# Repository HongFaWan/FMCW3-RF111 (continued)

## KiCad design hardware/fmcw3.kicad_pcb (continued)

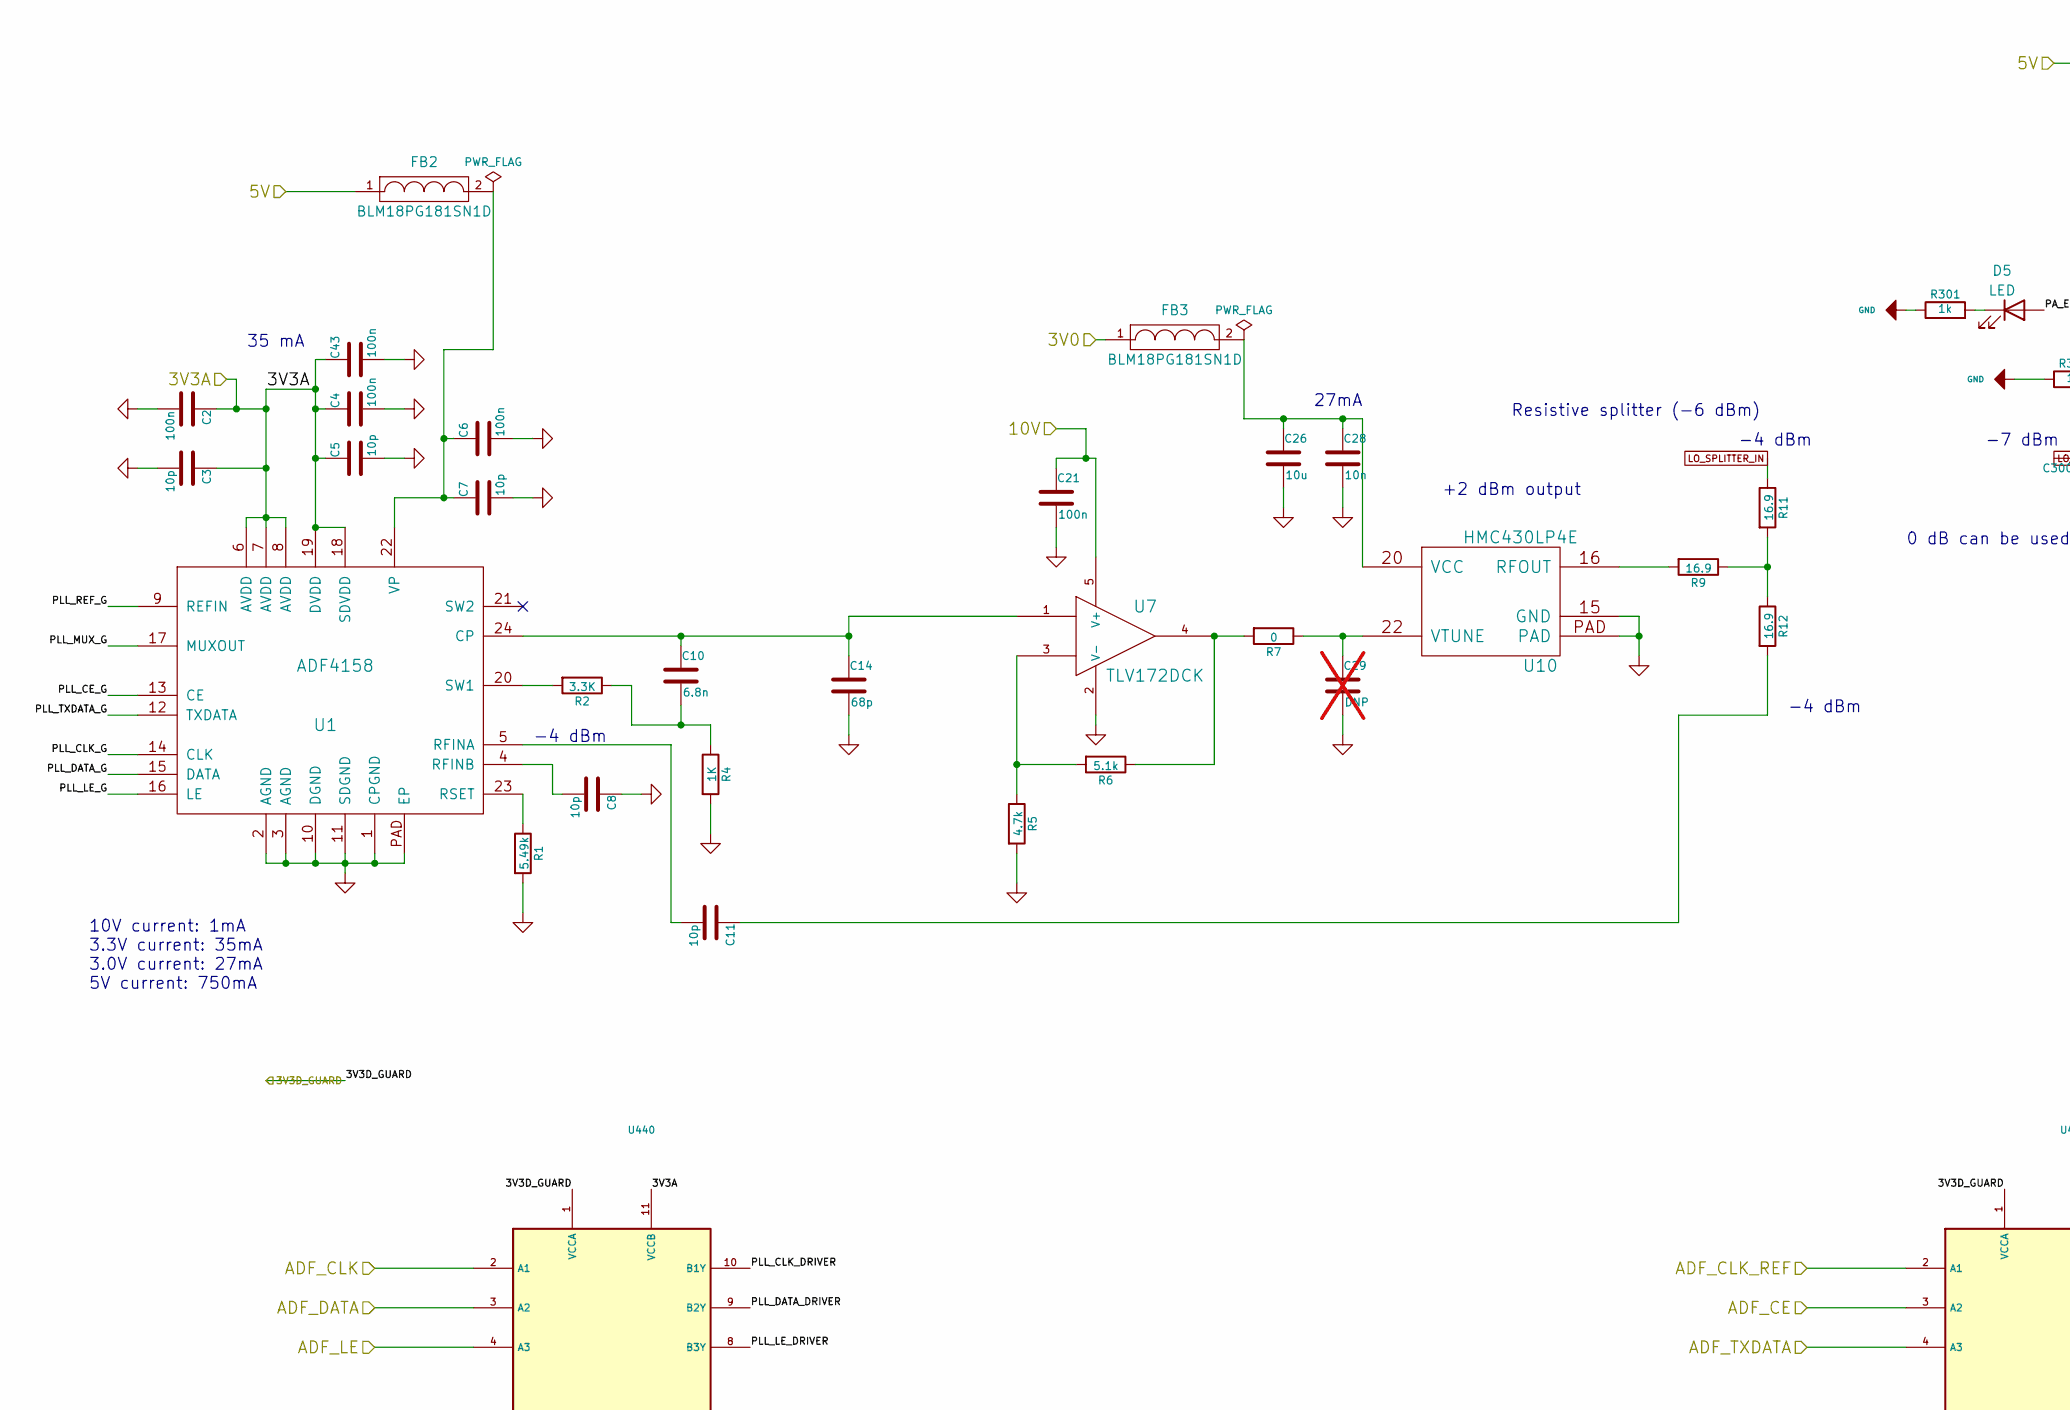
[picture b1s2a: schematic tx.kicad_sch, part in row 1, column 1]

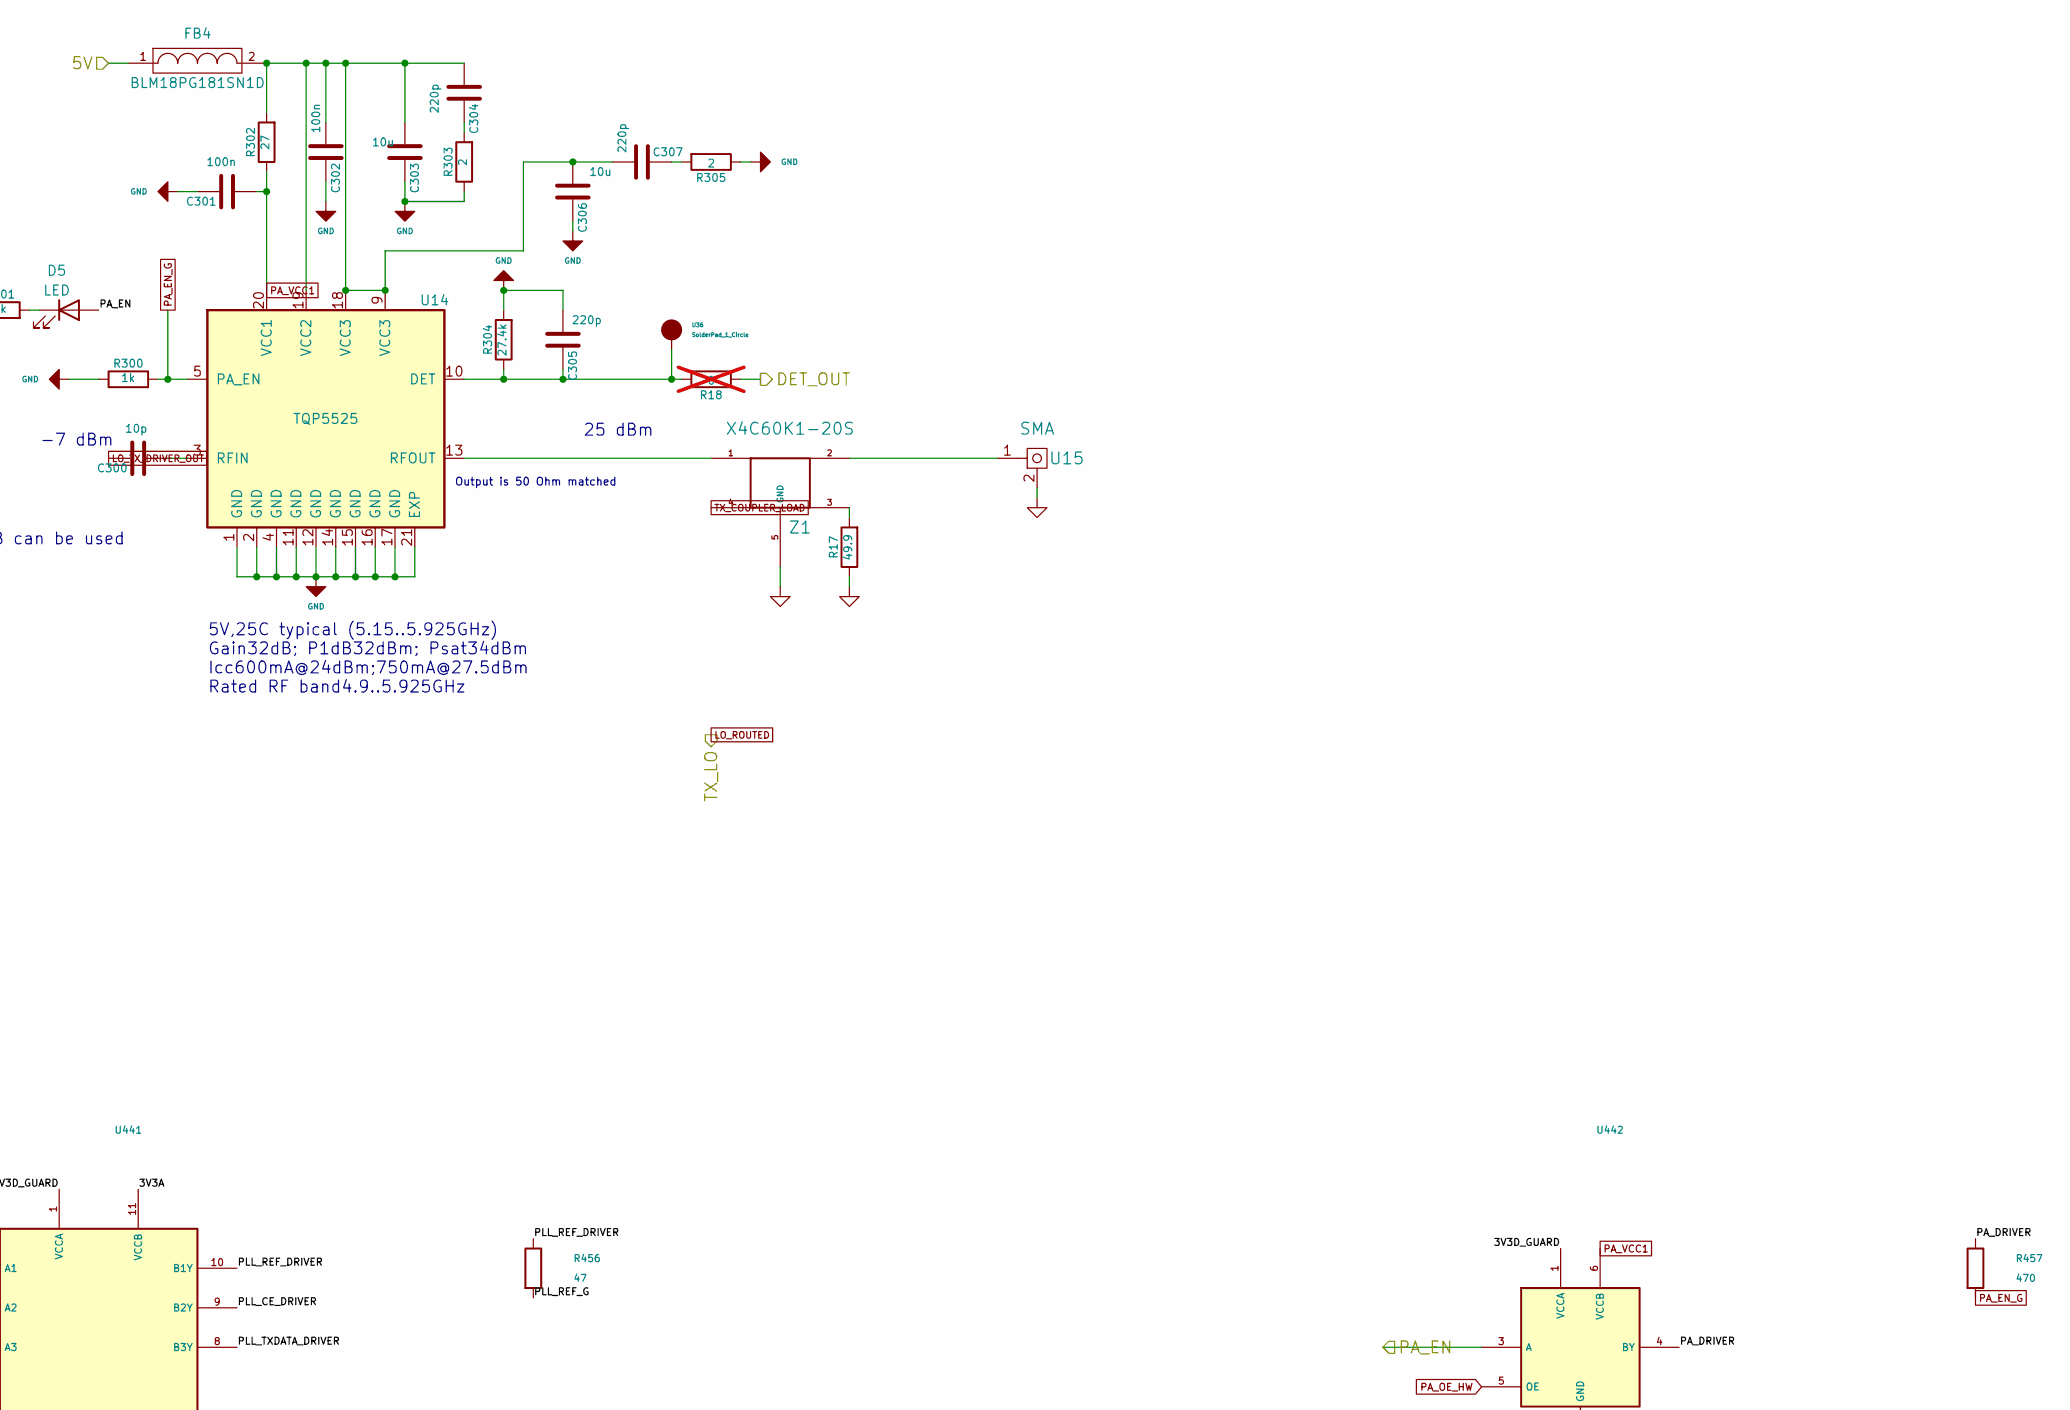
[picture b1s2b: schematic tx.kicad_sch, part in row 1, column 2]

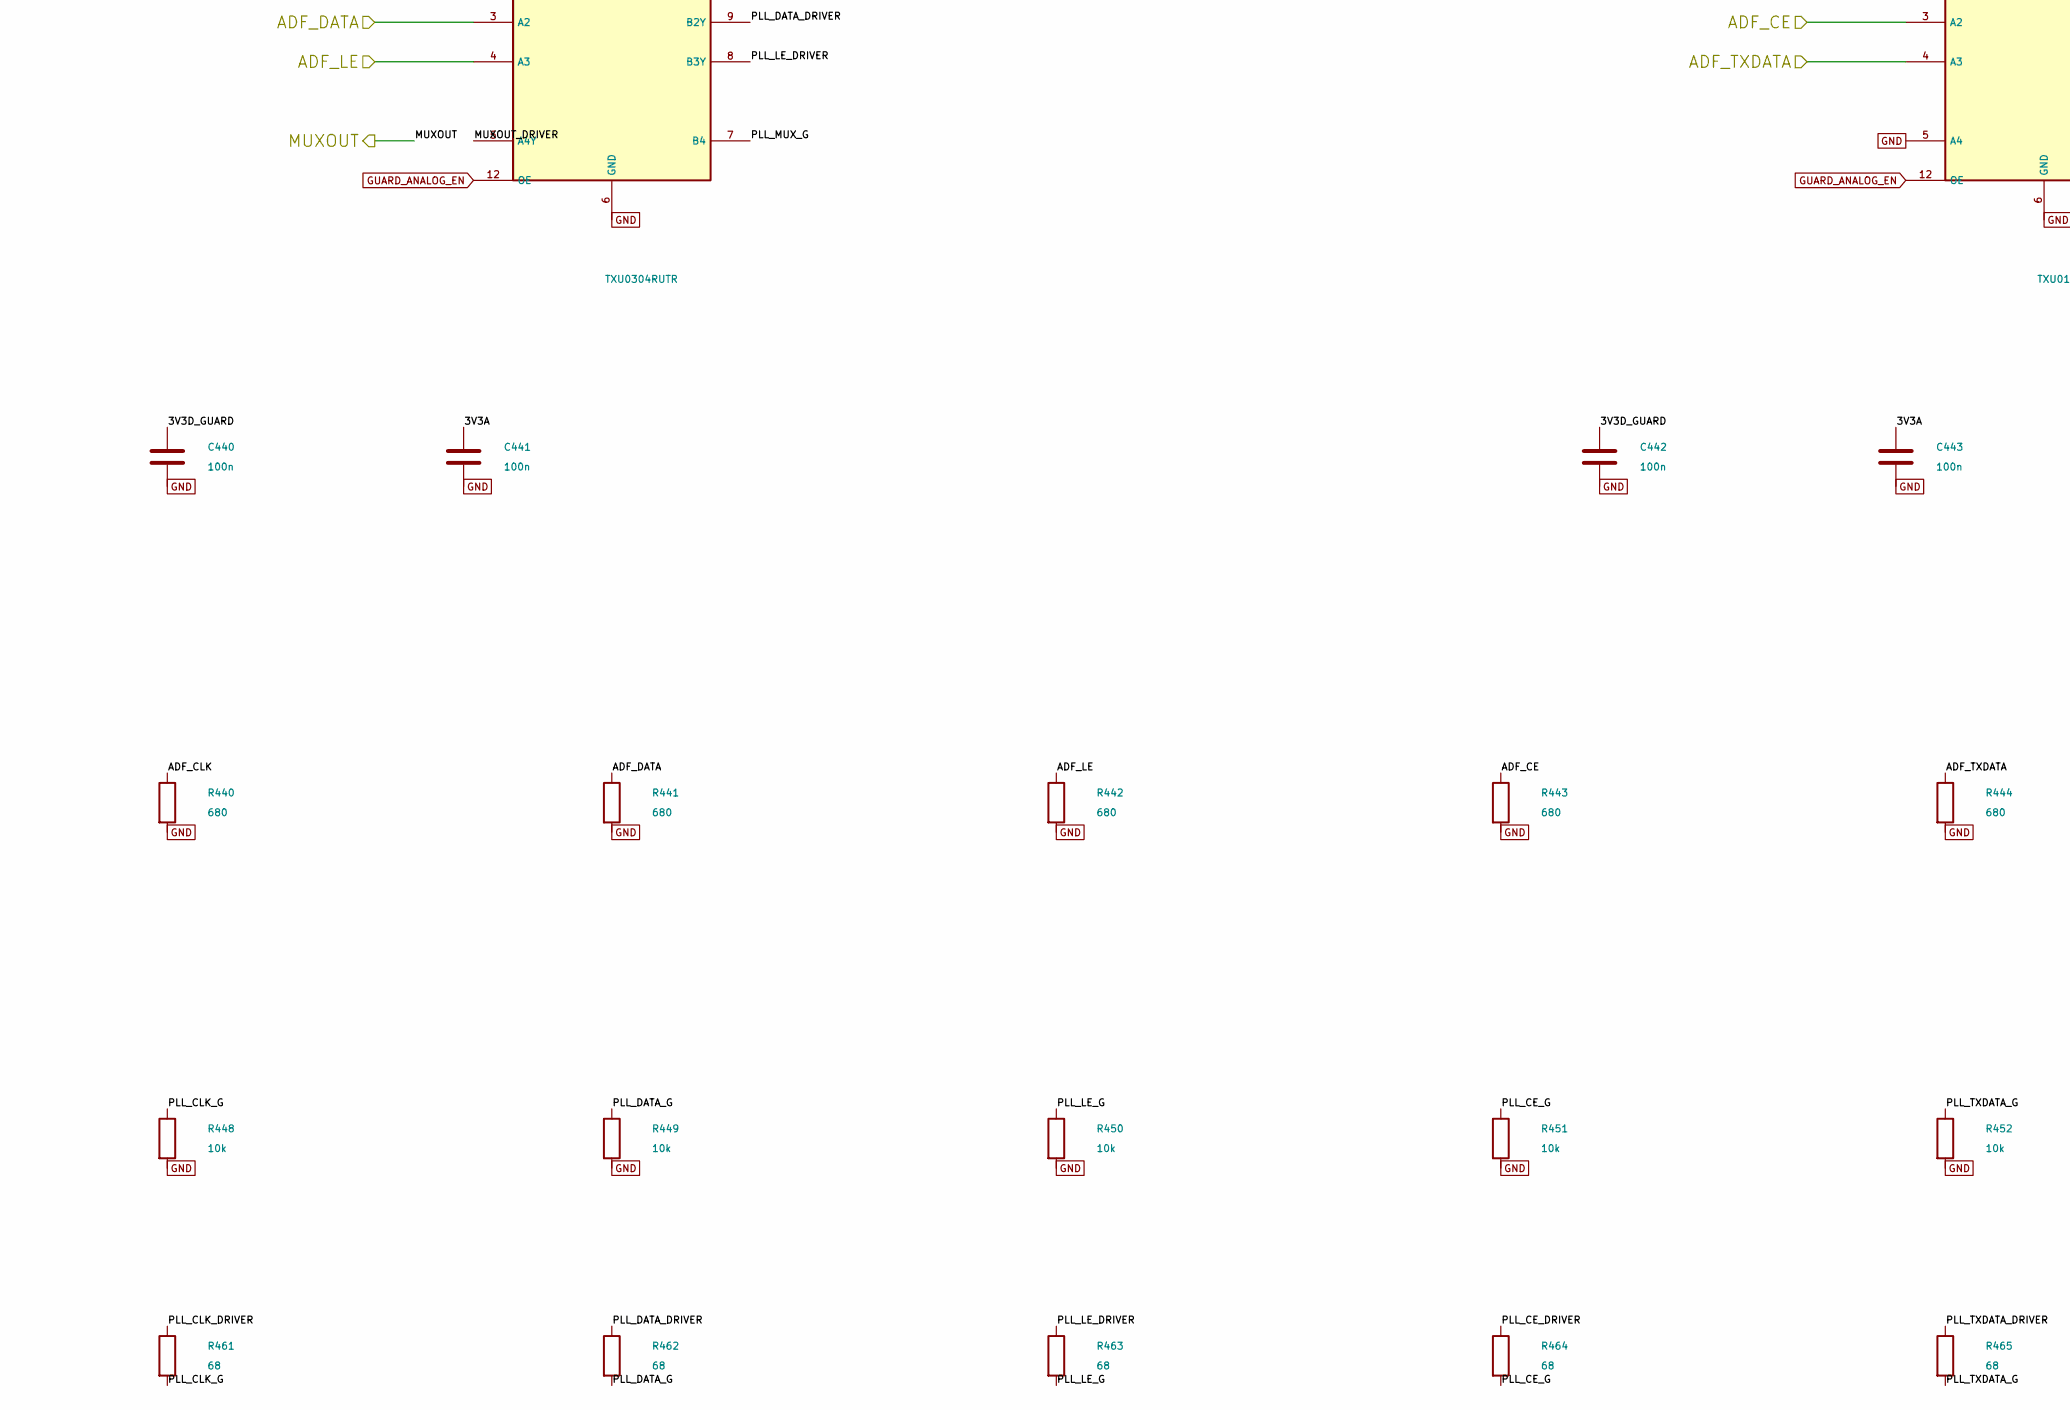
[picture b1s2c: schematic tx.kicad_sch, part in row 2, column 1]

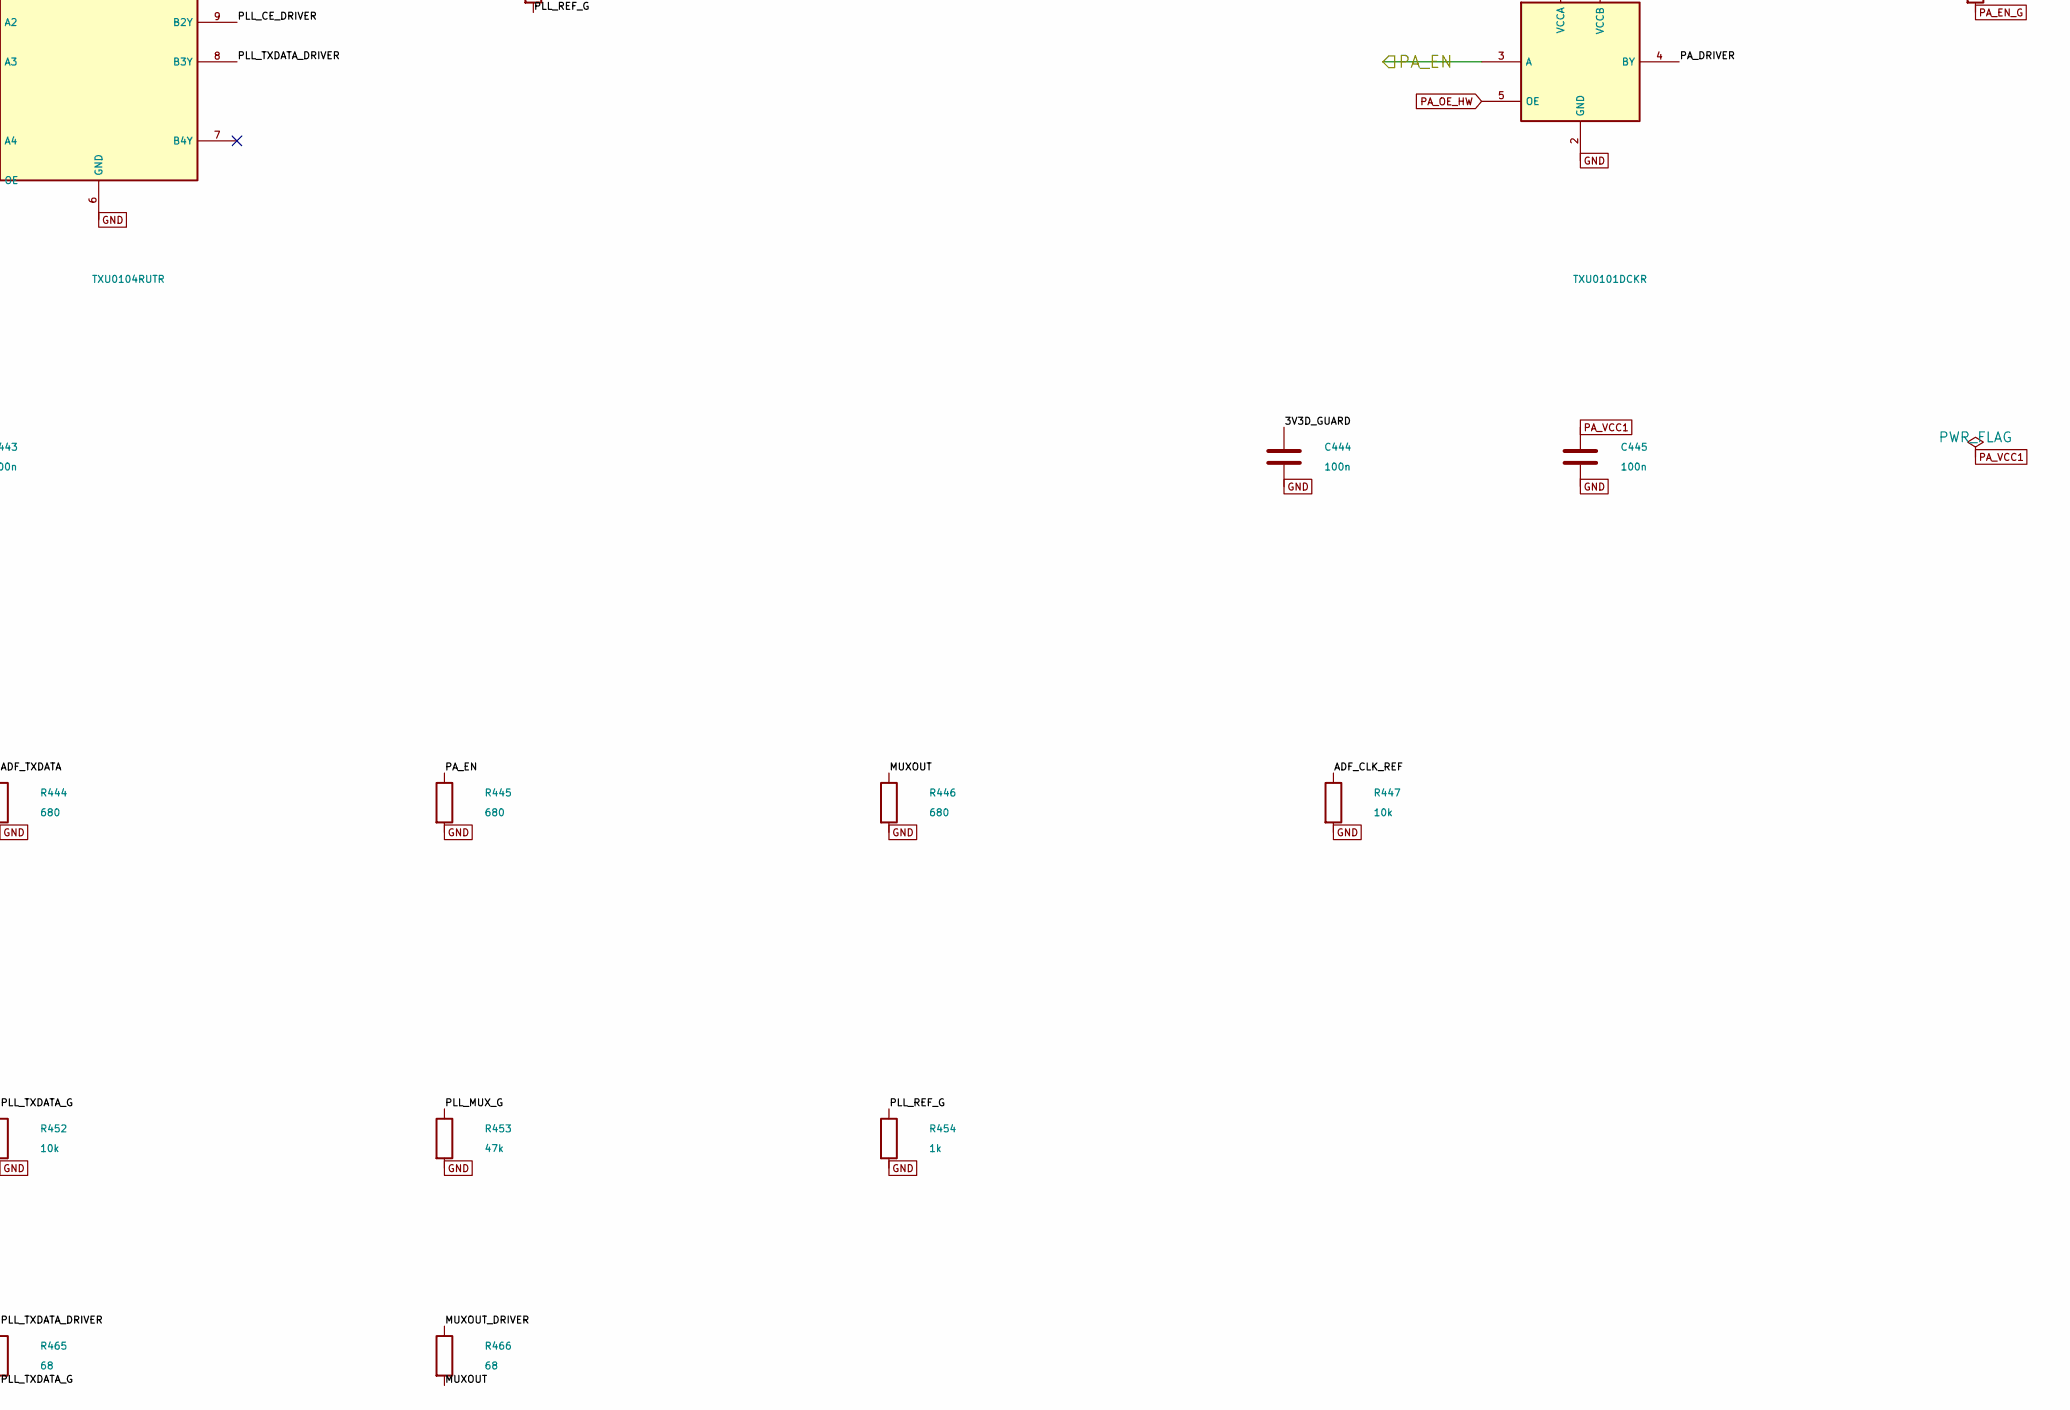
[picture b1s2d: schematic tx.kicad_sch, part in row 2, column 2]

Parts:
C2, C4, C6, C21, C43, C301, C302: 100n; SMD_0402
C3, C5, C7, C8, C11, C300: 10p; SMD_0402
C10: 6.8n; SMD_0402
C14: 68p; SMD_0402
C26, C303, C306: 10u; SMD_0805
C28: 10n; SMD_0402
C29: DNP; SMD_0402; not fitted
C304, C305, C307: 220p; SMD_0402
C440, C441, C442, C443, C444, C445: 100n; C_0402_Murata_GRM155_Mount22; Voltage 50V; Tolerance 10%; MPN GRM155R71H104KE14D; LCSC C77020
D5: LED; Diode_0603
FB2, FB3, FB4: BLM18PG181SN1D; SMD_0603
R1: 5.49k; SMD_0402
R2: 3.3K; SMD_0402
R4: 1K; SMD_0402
R5: 4.7k; SMD_0402
R6: 5.1k; SMD_0402; MPN RC0402FR-075K1L; LCSC C105872
R7: 0; SMD_0402
R9, R11, R12: 16.9; SMD_0402
R17: 49.9; SMD_0402
R18: 0; SMD_0402; not fitted
R300, R301: 1k; SMD_0402
R302: 27; SMD_0402
R303, R305: 2; SMD_0603
R304: 27.4k; SMD_0402
R440, R441, R442, R443, R444, R445, R446: 680; R_0402_Yageo_Mount22; MPN RC0402FR-07680RL; LCSC C137948
R447, R448, R449, R450, R451, R452: 10k; R_0402_Yageo_Mount22; MPN RT0402BRD0710KL; LCSC C190095
R453: 47k; R_0402_Yageo_Mount22; MPN RC0402FR-0747KL; LCSC C93943
R454: 1k; R_0402_Yageo_Mount22; MPN RC0402FR-071KL; LCSC C106235
R456: 47; R_0402_Yageo_Mount22; MPN RC0402FR-0747RL; LCSC C137973
R457: 470; R_0402_Yageo_Mount22; MPN RC0402FR-07470RL
R461, R462, R463, R464, R465, R466: 68; R_0402_Yageo_Mount22; MPN RC0402FR-0768RL; LCSC C163455
U1: ADF4158; VFQFN-24
U7: TLV172DCK; SOT-353_SC-70-5
U10: HMC430LP4E; VQFN-24; MPN HMC430LP4ETR
U14: TQP5525; QFN-20-1EP_4x4mm_P0.5mm_EP2.5x2.5mm_ThermalVias
U15: SMA; CONSMA003.062
U36: SolderPad_1_Circle; SolderPad_1_1.5mm_SMD_Circle
U440: TXU0304RUTR; TI_RUT12_0p7x0p2_MFR; MPN TXU0304RUTR; LCSC C2959768
U441: TXU0104RUTR; TI_RUT12_0p7x0p2_MFR; MPN TXU0104RUTR; LCSC C5187176
U442: TXU0101DCKR; TI_DCK6_0p9x0p4_MFR; MPN TXU0101DCKR; LCSC C5217868
Z1: X4C60K1-20S; X4C60K1_20S; MPN X4C60K1-20S

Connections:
/3V0: FB3.1; also elsewhere on the board
/3V3A: C2.1, C3.1, C4.1, C5.1, C43.1, C441.1, C443.1, U1.6 (AVDD), U1.7 (AVDD), U1.8 (AVDD), U1.18 (SDVDD), U1.19 (DVDD), U440.11 (VCCB), U441.11 (VCCB); also elsewhere on the board
/5V: FB2.1, FB4.1; also elsewhere on the board
/ADF_CE: R443.1, U441.3 (A2); also elsewhere on the board
/ADF_CLK: R440.1, U440.2 (A1); also elsewhere on the board
/ADF_CLK_REF: R447.1, U441.2 (A1); also elsewhere on the board
/ADF_DATA: R441.1, U440.3 (A2); also elsewhere on the board
/ADF_LE: R442.1, U440.4 (A3); also elsewhere on the board
/ADF_MUXOUT: R446.1, R466.2; also elsewhere on the board
/ADF_TXDATA: R444.1, U441.4 (A3); also elsewhere on the board
/DET_OUT: R18.1; also elsewhere on the board
/PA_EN: D5.2 (A), R445.1, U442.3 (A); also elsewhere on the board
/tx/MUXOUT_DRIVER: R466.1, U440.5 (A4Y)
/tx/PA_DRIVER: R457.1, U442.4 (BY)
/tx/PLL_CE_DRIVER: R464.1, U441.9 (B2Y)
/tx/PLL_CE_G: R451.1, R464.2, U1.13 (CE)
/tx/PLL_CLK_DRIVER: R461.1, U440.10 (B1Y)
/tx/PLL_CLK_G: R448.1, R461.2, U1.14 (CLK)
/tx/PLL_DATA_DRIVER: R462.1, U440.9 (B2Y)
/tx/PLL_DATA_G: R449.1, R462.2, U1.15 (DATA)
/tx/PLL_LE_DRIVER: R463.1, U440.8 (B3Y)
/tx/PLL_LE_G: R450.1, R463.2, U1.16 (LE)
/tx/PLL_MUX_G: R453.1, U1.17 (MUXOUT), U440.7 (B4)
/tx/PLL_REF_DRIVER: R456.1, U441.10 (B1Y)
/tx/PLL_REF_G: R454.1, R456.2, U1.9 (REFIN)
/tx/PLL_TXDATA_DRIVER: R465.1, U441.8 (B3Y)
/tx/PLL_TXDATA_G: R452.1, R465.2, U1.12 (TXDATA)
GND: C2.2, C3.2, C4.2, C5.2, C6.2, C7.2, C8.1, C14.2, C21.2, C26.2, C28.2, C29.2, C43.2, C301.1, C302.1, C303.1, C305.2, C306.1, C440.2, C441.2, C442.2, C443.2, C444.2, C445.2, R1.2, R4.2, R5.2, R17.1, R300.1, R301.1, R303.1, R304.2, R305.1, R440.2, R441.2, R442.2, R443.2, R444.2, R445.2, R446.2, R447.2, R448.2, R449.2, R450.2, R451.2, R452.2, R453.2, R454.2, U1.1 (CPGND), U1.2 (AGND), U1.3 (AGND), U1.10 (DGND), U1.11 (SDGND), U1.PAD (EP), U7.2 (V-), U10.15 (GND), U10.PAD, U14.1 (GND), U14.2 (GND), U14.4 (GND), U14.11 (GND), U14.12 (GND), U14.14 (GND), U14.15 (GND), U14.16 (GND), U14.17 (GND), U14.21 (EXP), U15.2, U440.6 (GND), U441.5 (A4), U441.6 (GND), U442.2 (GND), Z1.5 (GND); also elsewhere on the board
GUARD_ANALOG_EN: U440.12 (OE), U441.12 (OE); also elsewhere on the board
LO_SPLITTER_IN: R11.1; also elsewhere on the board
LO_TX_DRIVER_OUT: C300.1; also elsewhere on the board
unnamed: C10.2, R2.1, R4.1
unnamed: C11.1, R12.2
unnamed: C304.1, R303.2
unnamed: C307.1, R305.2
unnamed: D5.1 (K), R301.2
unnamed: R5.1, R6.2, U7.3
unnamed: R6.1, R7.2, U7.4
unnamed: R9.1, R11.2, R12.1
unnamed: R17.2, Z1.3
unnamed: C10.1, C14.1, U1.24 (CP), U7.1
unnamed: C11.2, U1.5 (RFINA)
unnamed: C8.2, U1.4 (RFINB)
unnamed: R1.1, U1.23 (RSET)
unnamed: R2.2, U1.20 (SW1)
unnamed: C6.1, C7.1, FB2.2, U1.22 (VP)
unnamed: R9.2, U10.16 (RFOUT)
unnamed: C26.1, C28.1, FB3.2, U10.20 (VCC)
unnamed: C29.1, R7.1, U10.22 (VTUNE)
unnamed: C305.1, R18.2, R304.1, U14.10 (DET), U36.1
unnamed: C300.2, U14.3 (RFIN)
unnamed: U14.13 (RFOUT), Z1.1
unnamed: C302.2, C303.2, C304.2, C306.2, C307.2, FB4.2, R302.2, U14.9 (VCC3), U14.18 (VCC3), U14.19 (VCC2)
unnamed: U15.1, Z1.2
PA_EN_G: R300.2, R457.2, U14.5 (PA_EN); also elsewhere on the board
PA_OE_HW: U442.5 (OE); also elsewhere on the board
PA_VCC1: C301.2, C445.1, R302.1, U14.20 (VCC1), U442.6 (VCCB); also elsewhere on the board
TUNE_10V: C21.1, U7.5 (V+); also elsewhere on the board
TX_COUPLER_LOAD: Z1.4; also elsewhere on the board

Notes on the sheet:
Resistive splitter (-6 dBm)
-4 dBm
10V current: 1mA 3.3V current: 35mA 3.0V current: 27mA 5V current: 750mA
+2 dBm output
35 mA
-7 dBm
27mA
Output is 50 Ohm matched
5V,25C typical (5.15..5.925GHz) Gain32dB; P1dB32dBm; Psat34dBm Icc600mA@24dBm;750mA@27.5dBm Rated RF band4.9..5.925GHz
0 dB can be used
25 dBm

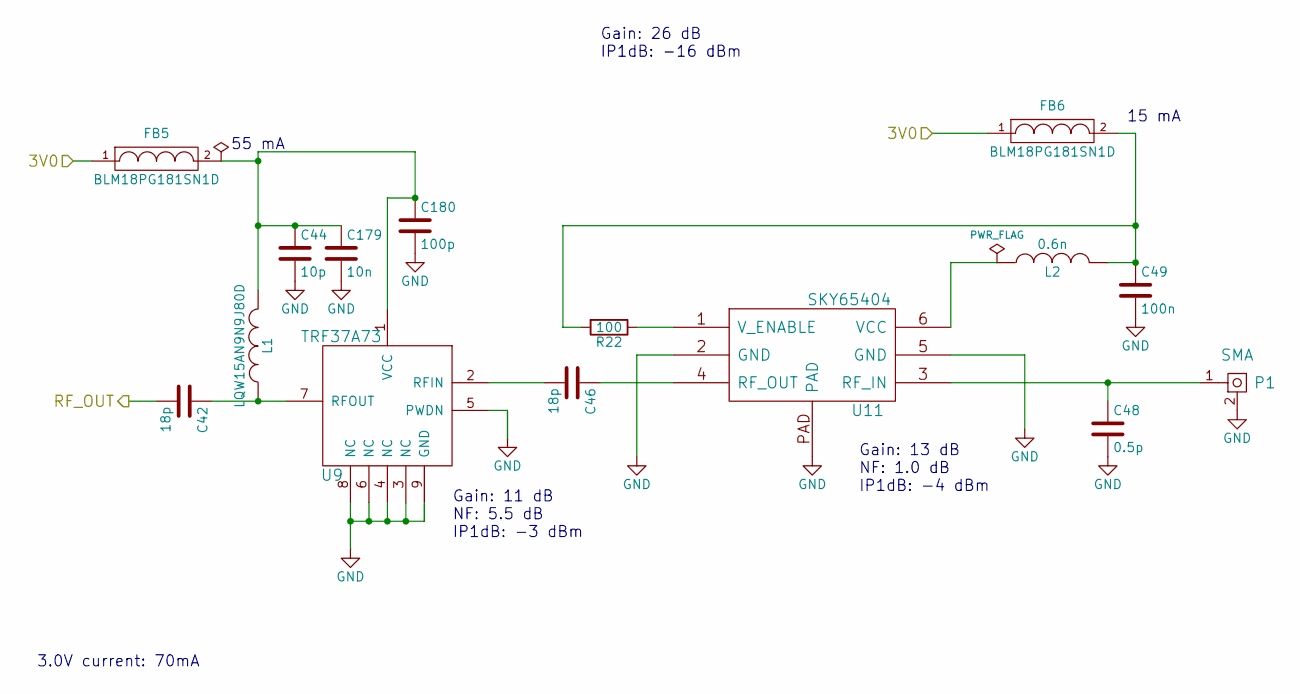
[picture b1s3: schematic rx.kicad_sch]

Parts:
C42, C46: 18p; SMD_0402
C44: 10p; SMD_0402
C48: 0.5p; SMD_0402
C49: 100n; SMD_0402
C179: 10n; SMD_0402
C180: 100p; SMD_0402
FB5, FB6: BLM18PG181SN1D; SMD_0603
L1: LQW15AN9N9J80D; SMD_0402
L2: 0.6n; SMD_0402
P1: SMA; CONSMA003.062
R22: 100; SMD_0402
U9: TRF37A73; DFN-8-1EP_2x2mm_Pitch0.5mm
U11: SKY65404; XFDFN-6

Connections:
/3V0: FB5.1, FB6.1; also elsewhere on the board
/RF1: C42.2; also elsewhere on the board
GND: C44.2, C48.2, C49.2, C179.2, C180.2, P1.2, U9.3 (NC), U9.4 (NC), U9.5 (PWDN), U9.6 (NC), U9.8 (NC), U9.9 (GND), U11.2 (GND), U11.5 (GND), U11.PAD; also elsewhere on the board
unnamed: C49.1, FB6.2, L2.2, R22.2
unnamed: C46.2, U9.2 (RFIN)
unnamed: C42.1, L1.1, U9.7 (RFOUT)
unnamed: C44.1, C179.1, C180.1, FB5.2, L1.2, U9.1 (VCC)
unnamed: C48.1, P1.1, U11.3 (RF_IN)
unnamed: C46.1, U11.4 (RF_OUT)
unnamed: L2.1, U11.6 (VCC)
unnamed: R22.1, U11.1 (V_ENABLE)

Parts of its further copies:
C52, C55: 18p; SMD_0402
C53: 10p; SMD_0402
C57: 0.5p; SMD_0402
C58: 100n; SMD_0402
C206: 10n; SMD_0402
C213: 100p; SMD_0402
FB7, FB8: BLM18PG181SN1D; SMD_0603
L3: LQW15AN9N9J80D; SMD_0402
L4: 0.6n; SMD_0402
P2: SMA; CONSMA003.062
R23: 100; SMD_0402
U13: TRF37A73; DFN-8-1EP_2x2mm_Pitch0.5mm
U16: SKY65404; XFDFN-6

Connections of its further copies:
/3V0: FB7.1, FB8.1; also elsewhere on the board
/RF2: C52.2; also elsewhere on the board
GND: C53.2, C57.2, C58.2, C206.2, C213.2, P2.2, U13.3 (NC), U13.4 (NC), U13.5 (PWDN), U13.6 (NC), U13.8 (NC), U13.9 (GND), U16.2 (GND), U16.5 (GND), U16.PAD; also elsewhere on the board
unnamed: C58.1, FB8.2, L4.2, R23.2
unnamed: C55.2, U13.2 (RFIN)
unnamed: C52.1, L3.1, U13.7 (RFOUT)
unnamed: C53.1, C206.1, C213.1, FB7.2, L3.2, U13.1 (VCC)
unnamed: C57.1, P2.1, U16.3 (RF_IN)
unnamed: C55.1, U16.4 (RF_OUT)
unnamed: L4.1, U16.6 (VCC)
unnamed: R23.1, U16.1 (V_ENABLE)

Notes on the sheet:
Gain: 11 dB NF: 5.5 dB IP1dB: -3 dBm
15 mA
Gain: 13 dB NF: 1.0 dB IP1dB: -4 dBm
3.0V current: 70mA
55 mA
Gain: 26 dB IP1dB: -16 dBm
